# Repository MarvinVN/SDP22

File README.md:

# SDP22

For website run in terminal
    cd frontend
    npm start
    * this should open a browser so you can see your development

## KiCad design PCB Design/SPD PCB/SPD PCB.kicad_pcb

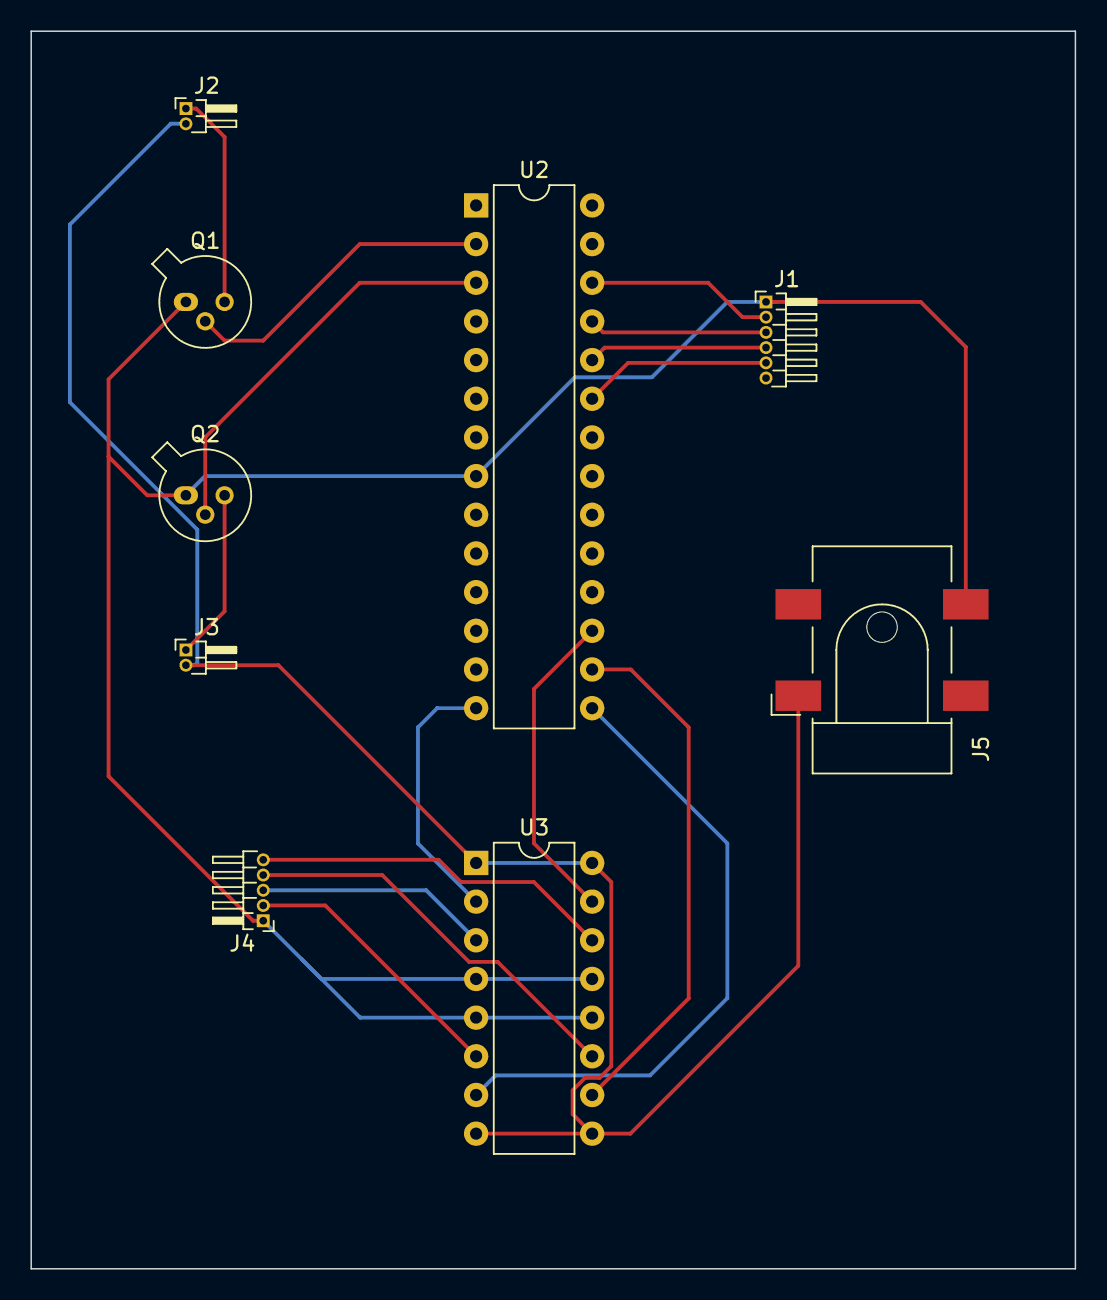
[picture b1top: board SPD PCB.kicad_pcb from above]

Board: 2 copper layers, 68.6 x 81.3 mm, 9 parts (0 on the bottom side), 18 nets.

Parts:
J1: Conn_01x06_Male; PinHeader_1x06_P1.00mm_Horizontal
J2, J3: Conn_01x02_Female; PinHeader_1x02_P1.00mm_Horizontal
J4: Conn_01x05_Male; PinHeader_1x05_P1.00mm_Horizontal
J5: Barrel_Jack; BarrelJack_CLIFF_FC681465S_SMT_Horizontal
Q1, Q2: 2N2647; TO-18-3
U2: ATmega328-P; DIP-28_W7.62mm
U3: L293D; DIP-16_W7.62mm

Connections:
+5V: J2.2, J3.2, J5.1, U3.1 (EN1,2), U3.8 (VCC2), U3.9 (EN3,4), U3.16 (VCC1)
Earth: J1.1, J4.1, J5.2, Q1.1 (B2), Q2.1 (B2), U2.8 (GND), U3.4 (GND), U3.5 (GND), U3.12 (GND), U3.13 (GND)
unnamed: J1.2, U2.26 (PC3)
unnamed: J1.3, U2.25 (PC2)
unnamed: J1.4, U2.24 (PC1)
unnamed: J1.5, U2.23 (PC0)
unnamed: J2.1, Q1.3 (B1)
unnamed: J4.2, U3.6 (2Y)
unnamed: Q1.2 (E), U2.2 (PD0)
unnamed: Q2.2 (E), U2.3 (PD1)
unnamed: J3.1, Q2.3 (B1)
unnamed: U2.14 (PB0), U3.2 (1A)
unnamed: U2.15 (PB1), U3.7 (2A)
unnamed: U2.16 (PB2), U3.10 (3A)
unnamed: U2.17 (PB3), U3.15 (4A)
unnamed: J4.3, U3.3 (1Y)
unnamed: J4.4, U3.11 (3Y)
unnamed: J4.5, U3.14 (4Y)

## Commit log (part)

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2022-04-12 multiplayer w/ hardware working
2022-04-13 adding multi codes
2022-04-13 adding file for blackjack.py
2022-04-13 low card shuffle implemented
2022-04-13 update gui
2022-04-14 hardware
2022-04-14 go[jdsh
2022-04-15 fully integrated multi hw buttons
2022-04-19 edits
2022-04-19 edit
2022-04-19 woeih
2022-04-19 QoL gameplay changes
2022-04-19 double implemented
2022-04-21 checkValue edits
2022-04-21 added getWallets
2022-04-21 removing uncomments
2022-04-21 commented out rfid pn532 config in game
2022-04-21 fix positional args
2022-04-22 adding prints
2022-04-22 debugging
2022-04-22 prints
2022-04-22 importing time
2022-04-22 commenting out some messages
2022-04-22 commented out timer
2022-04-22 added gs
2022-04-22 fixed args for player.draw
2022-04-22 commented out fourth buttons
2022-04-22 reconfiguring button pinouts
2022-04-22 added str(
2022-04-22 removed exit button gui
2022-04-25 can only double on first move (can't double after a hit)
2022-04-25 testing maximizing first window
2022-04-25 adding paths to svg
2022-04-25 added _ for blackjack path
2022-04-25 change monitor sizing
2022-04-26 testing dimensions
2022-04-26 adding game without hardware
2022-04-26 dims
2022-04-26 fonts
2022-04-27 sizing
2022-04-27 change dimensions
2022-04-27 changing dealer sizing, add back card
2022-04-27 background
2022-04-27 green
2022-04-27 colors
2022-04-27 colors, multiplayer sizing
2022-04-27 fix dealer and colors
2022-04-27 testing colors
2022-04-27 testing
2022-04-27 change color
2022-04-27 trying to fix gui next round
2022-04-27 trying to fix next round gui
2022-04-27 fixing next round; moved done_round function
2022-04-27 added eb connection
2022-04-27 eb connection
2022-04-27 remove code in confirm connection
2022-04-27 uncommenting done_Roudn
2022-04-29 adding wait delay
2022-04-29 lkjhgfd
2022-04-29 commented done_Round (only allow one round for now)
2022-04-29 commenting out more code
2022-04-29 add sys exit
